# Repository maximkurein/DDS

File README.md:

<p align="center">

</p>

<p align="center">
  <a href="#скачать"><strong>Скачать DDS Studio</strong></a>
  &nbsp;·&nbsp; <a href="#плата">Плата</a>
  &nbsp;·&nbsp; <a href="#прошивка">Прошивка</a>
  &nbsp;·&nbsp; <a href="#dds-studio">DDS Studio</a>
  &nbsp;·&nbsp; <a href="USER_GUIDE.md">Руководство</a>
  &nbsp;·&nbsp; <a href="README_RU.md">Инженерные подробности</a>
</p>

Синтезатор частоты **48–52 МГц** с шагом **1 кГц** и выходом **−10 дБм на 50 Ом**. Сигнал формирует прямой цифровой синтезатор **1508ПЛ8Т** (АО НПЦ «ЭЛВИС») от такта 480 МГц, управляет им контроллер **1887ВЕ7Т**. Частоту задают DIP-переключатели или компьютер через USB-UART и приложение **DDS Studio**.

В репозитории всё изделие: проект платы в KiCad с конструкторской документацией по ГОСТ ЕСКД, прошивка контроллера и настольное приложение для управления и изучения DDS.

<p align="center">
  
  <br><sub>Ревизия F, 120×50 мм, 4 слоя. Рендер KiCad 10 из <code>DDS_48_52.kicad_pcb</code>.</sub>
</p>

## Из чего состоит

| | Часть | Что внутри | Где |
|---|---|---|---|
| 🧩 | **Плата** | схема на 3 листах, плата 4 слоя, Gerber/BOM/CPL для JLCPCB, Э3 и ПЭ3 | [`DDS_48_52.kicad_pro`](DDS_48_52.kicad_pro), [`output/`](output) |
| ⚙️ | **Прошивка D2** | запуск 1508ПЛ8Т по SPI, частота с DIP, бесшовная смена, команды по UART | [`firmware/`](firmware) |
| 🖥️ | **DDS Studio** | регистры, расчёт частоты и спектра, виртуальная плата, опыты, уроки | [`studio/`](studio) |

## Скачать

**DDS Studio 0.3.1 для macOS и Windows** — на странице [релизов](https://github.com/maximkurein/DDS/releases/latest):

| Файл | Что это |
|---|---|
| `DDS-Studio-v0.3.1-macos-universal.dmg` | macOS (Apple Silicon и Intel): перетащите DDS Studio в «Программы» |
| `DDS-Studio-v0.3.1-macos-universal.app.zip` | то же приложение без образа диска |
| `DDS-Studio-v0.3.1-windows-x64-setup.exe` | Windows 10/11: установщик, ярлык в меню «Пуск» и на рабочем столе |
| `DDS-Studio-v0.3.1-windows-x64.zip` | тот же `DDS Studio.exe` без мастера установки |
| `checksum.txt` | контрольные суммы SHA-256 |

Приложение не подписано. Windows SmartScreen: «Подробнее» → «Выполнить в любом случае». macOS при первом запуске: правый клик по приложению → «Открыть», или

```bash
xattr -dr com.apple.quarantine "/Applications/DDS Studio.app"
```

Без платы приложение работает с **виртуальной платой**: все экраны и опыты доступны сразу. Windows и веб-режим собираются из исходников — см. [studio/BUILD.md](studio/BUILD.md).

## Плата

| Узел | Что |
|---|---|
| DDS | 1508ПЛ8Т (D1): 48-битный аккумулятор фазы, 10-битный ЦАП, такт 480 МГц |
| Контроллер | 1887ВЕ7Т (D2), +5 В, тактирование от внутреннего RC 8 МГц |
| Выход | ФНЧ 7-го порядка (срез ≈ 70 МГц) и аттенюатор → XW2, −10 дБм на 50 Ом |
| Такт | S1: внешний вход XW1 или генератор G1 (не устанавливается) |
| Частота | DIP S2 (8 разрядов) + S3 (4 разряда), кнопка «Применить» S4 |
| Связь с ПК | USB-UART на площадках X1, 38400 8N1, логика 5 В |
| Питание | +15 В → DC/DC 1393ЕУ014 (+5 В) → LDO 1158ЕН3.3ВХ (+3,3 В), 1325ЕН1.8У (+1,8 В) |
| Конструкция | 120×50 мм, 4 слоя, JLC04161H-7628, ENIG |

<table>
  <tr>
    <td width="50%"><br><sub><b>Сверху.</b> D1 — справа, D2 — в центре, DIP S2/S3 и кнопка S4 внизу, SMA XW1 (такт) и XW2 (выход).</sub></td>
    <td width="50%"><br><sub><b>Снизу.</b> Элементов нет: полигон земли, сшивка переходными отверстиями по краям, выводы DIP и SMA.</sub></td>
  </tr>
</table>

**Статус.** ERC 0, DRC со сверкой со схемой 0, соединения совпадают с эталоном ревизии F. Это **ещё не выпуск в производство**: посадочные места новых отечественных элементов — заполнители до получения чертежей корпусов, генератор G1 не подтверждён паспортом, нагрев 1325ЕН1.8У и устойчивость 1393ЕУ014 нужно проверить. Подробно — [README_RU.md](README_RU.md), [docs/REVISION_F.md](docs/REVISION_F.md), [docs/design_notes.md](docs/design_notes.md).

Схема и плата открываются в KiCad 10: `DDS_48_52.kicad_pro`. PDF схемы и сборочного чертежа — в [`output/pdf/`](output/pdf), файлы для заказа — в [`output/jlcpcb/`](output/jlcpcb).

## Прошивка

Прошивка контроллера D2 написана на C (avr-gcc, CMake), собирается и прошивается из VS Code/Cursor через JTAG (X3).

- После включения ждёт питание DDS, сбрасывает и настраивает 1508ПЛ8Т, ставит частоту с DIP-переключателей.
- Новая частота включается кнопкой S4 **без разрыва фазы**: запись в неактивный профиль и переключение `SEL_REG`.
- С версии **1.1.0** принимает команды по UART (`?`, `REMOTE`, `W`, `R`, `S`, `RST`, `HOP`, `ST`): в режиме `REMOTE` частотой управляет компьютер.
- Логика проверяется на ПК host-тестами с подменой SPI и таймеров (`cmake --preset host-tests`).

Подробно — [firmware/README.md](firmware/README.md), первая прошивка платы — [USER_GUIDE.md](USER_GUIDE.md).

## DDS Studio

Настольное приложение для управления платой и изучения DDS: ядро на Rust, нативный интерфейс на egui (без WebView) для macOS и Windows, плюс веб-режим на React. Интерфейс на русском.

<p align="center">
  
  <br><sub>Живая блок-схема 1508ПЛ8Т: нажмите на блок — справа его параметры и поля регистров. Снимки — DDS Studio 0.3.0 (egui).</sub>
</p>

<table>
  <tr>
    <td width="50%"><br><sub><b>Частота.</b> Приращение фазы dPh, ошибка сетки, DIP-код, ожидаемый уровень на XW2 и подбор амплитуды.</sub></td>
    <td width="50%"><br><sub><b>Спектр.</b> Бит-в-бит модель канала и БПФ: несущая, гармоники, образы Fclk ± f, спуры усечения фазы.</sub></td>
  </tr>
  <tr>
    <td><br><sub><b>Тракт и шум.</b> АЧХ ФНЧ и аттенюатора с потерями катушек, sin(x)/x, фазовый шум и джиттер.</sub></td>
    <td><br><sub><b>Регистры.</b> 186 регистров по ТО, поля по битам, запись и чтение, экспорт в C-массив для прошивки.</sub></td>
  </tr>
  <tr>
    <td><br><sub><b>ЛЧМ.</b> Встроенный генератор линейной частотной модуляции: пила, треугольник, импульсный режим.</sub></td>
    <td><br><sub><b>Манипуляции.</b> ЧМн, ФМн-2/4/8, АМн, КАМ-16 на профилях с созвездием и последовательностью символов.</sub></td>
  </tr>
  <tr>
    <td><br><sub><b>Перебор.</b> 16 профилей канала 1; прошивка переключает их по таймеру (<code>HOP</code>).</sub></td>
    <td><br><sub><b>Свип.</b> Ступенчатая перестройка 48 → 52 МГц с бесшовной сменой частоты на каждой точке.</sub></td>
  </tr>
  <tr>
    <td><br><sub><b>Плата.</b> Вид по файлу KiCad, назначение каждого элемента, чек-лист первого включения.</sub></td>
    <td><br><sub><b>Подключение.</b> USB-UART, состояние платы (REMOTE, PGOOD, DIP), схема проводов и предупреждения.</sub></td>
  </tr>
  <tr>
    <td><br><sub><b>Академия.</b> 11 уроков от принципа DDS до протокола платы, из каждого — переход к опыту.</sub></td>
    <td><br><sub><b>Ревизии платы.</b> Как исправить плату в KiCad: мастер изменения T1–T8, матрица влияния, ворота ERC/DRC с командами.</sub></td>
  </tr>
  <tr>
    <td colspan="2"><br><sub><b>Светлая тема.</b> Переключается одной кнопкой в верхней панели.</sub></td>
  </tr>
</table>

Подробно о приложении — [studio/README.md](studio/README.md): подключение к плате, протокол, архитектура, сборка.

### Подключение к плате

| USB-UART адаптер | Плата | Сигнал D2 |
|---|---|---|
| RX | X1.1 | TXD0 (PE1) |
| TX | X1.4 | RXD0 (PE0) |
| GND | X1.6 | GND |

> [!WARNING]
> D2 работает от **+5 В** — нужен адаптер с логикой 5 В. Питание адаптера к плате **не подключать**. X1 — это и площадки ISP: на время ISP-программирования адаптер отсоединить. Такт на XW1 — от −10 до +5 дБм.

## Структура репозитория

```
DDS_48_52.kicad_pro, *.kicad_sch, *.kicad_pcb   проект KiCad (ревизия F)
lib/                                            символы, посадочные места, рамка ГОСТ
output/                                         PDF, BOM, нетлист, Gerber/CPL JLCPCB, Э3 (Visio), ПЭ3 (Word)
firmware/                                       прошивка D2 (1887ВЕ7Т), host-тесты
studio/                                         DDS Studio: Rust (egui) + веб-режим React
docs/                                           инженерные примечания, ревизии, уроки
tools/                                          генераторы схемы и платы, выпуск документов
.claude/skills/                                 скиллы Claude Code: разработка и ревизии плат
```

## Документация

| Документ | О чём |
|---|---|
| [START_HERE.md](START_HERE.md) | первый шаг на новой машине: клонирование, окружение, правила работы |
| [USER_GUIDE.md](USER_GUIDE.md) | руководство пользователя: подключение, частота, первая прошивка |
| [README_RU.md](README_RU.md) | плата подробно: листы схемы, пересборка, скрипты, история ревизий |
| [firmware/README.md](firmware/README.md) | прошивка: сборка, отладка, протокол UART (раздел 8.5) |
| [studio/README.md](studio/README.md) | DDS Studio: возможности, подключение, сборка |
| [studio/docs/PROTOCOL_ru.md](studio/docs/PROTOCOL_ru.md) | команды прошивки по UART |
| [docs/REVISION_F.md](docs/REVISION_F.md) | изменения ревизии F и состав КД |

Первоисточник по кристаллу — [ТО 1508ПЛ8Т](https://elvees.ru/typo11/mc/data_sheets/Manual_1508PL8T.pdf) (АО НПЦ «ЭЛВИС», ред. 14.10.2020). PDF производителей в репозиторий не кладём.

## Скиллы Claude Code

Технология «ТЗ → ЭРИ → схема → плата → документы → производство» и выпуск ревизий записаны как скиллы Claude Code в `.claude/skills/` и подхватываются при запуске Claude Code из корня репозитория:

- `pcb-design-pipeline` — сквозная разработка платы (KiCad, ГОСТ ЕСКД, JLCPCB);
- `pcb-revision-eco` — исправления и новая ревизия готовой платы.

Уроки проекта — в [docs/lessons.md](docs/lessons.md).

## Что ещё не проверено

- Плата ревизии F не изготовлена: работа на железе, уровень −10 дБм и тепловой режим не подтверждены.
- Прошивка 1.1.0 проверена host-тестами на ПК; сборка avr-gcc и UART на плате ещё не проверялись.
- Модель DDS Studio — инженерное приближение по ТО и схеме; уровень на XW2 уточняется измерением.

<details>
<summary><b>English summary</b></summary>

Frequency synthesizer 48–52 MHz, 1 kHz step, −10 dBm into 50 Ω, built around the 1508PL8T DDS (Elvees) clocked at 480 MHz and the 1887VE7T controller; board revision F, 120×50 mm, 4 layers, KiCad 10 with GOST ESKD documents and JLCPCB outputs. The repository also holds the controller firmware (C, CMake; UART command protocol since 1.1.0) and **DDS Studio**, a native Rust/egui desktop app (macOS, Windows) with a React web mode with a register map, frequency planner, bit-exact spectrum model, output-filter and phase-noise models, chirp and keying experiments, a virtual board and Russian lessons. Not a production release: new domestic parts still use placeholder land patterns and the board has not been built yet. The repository is mirrored on GitHub and a private Forgejo.

</details>

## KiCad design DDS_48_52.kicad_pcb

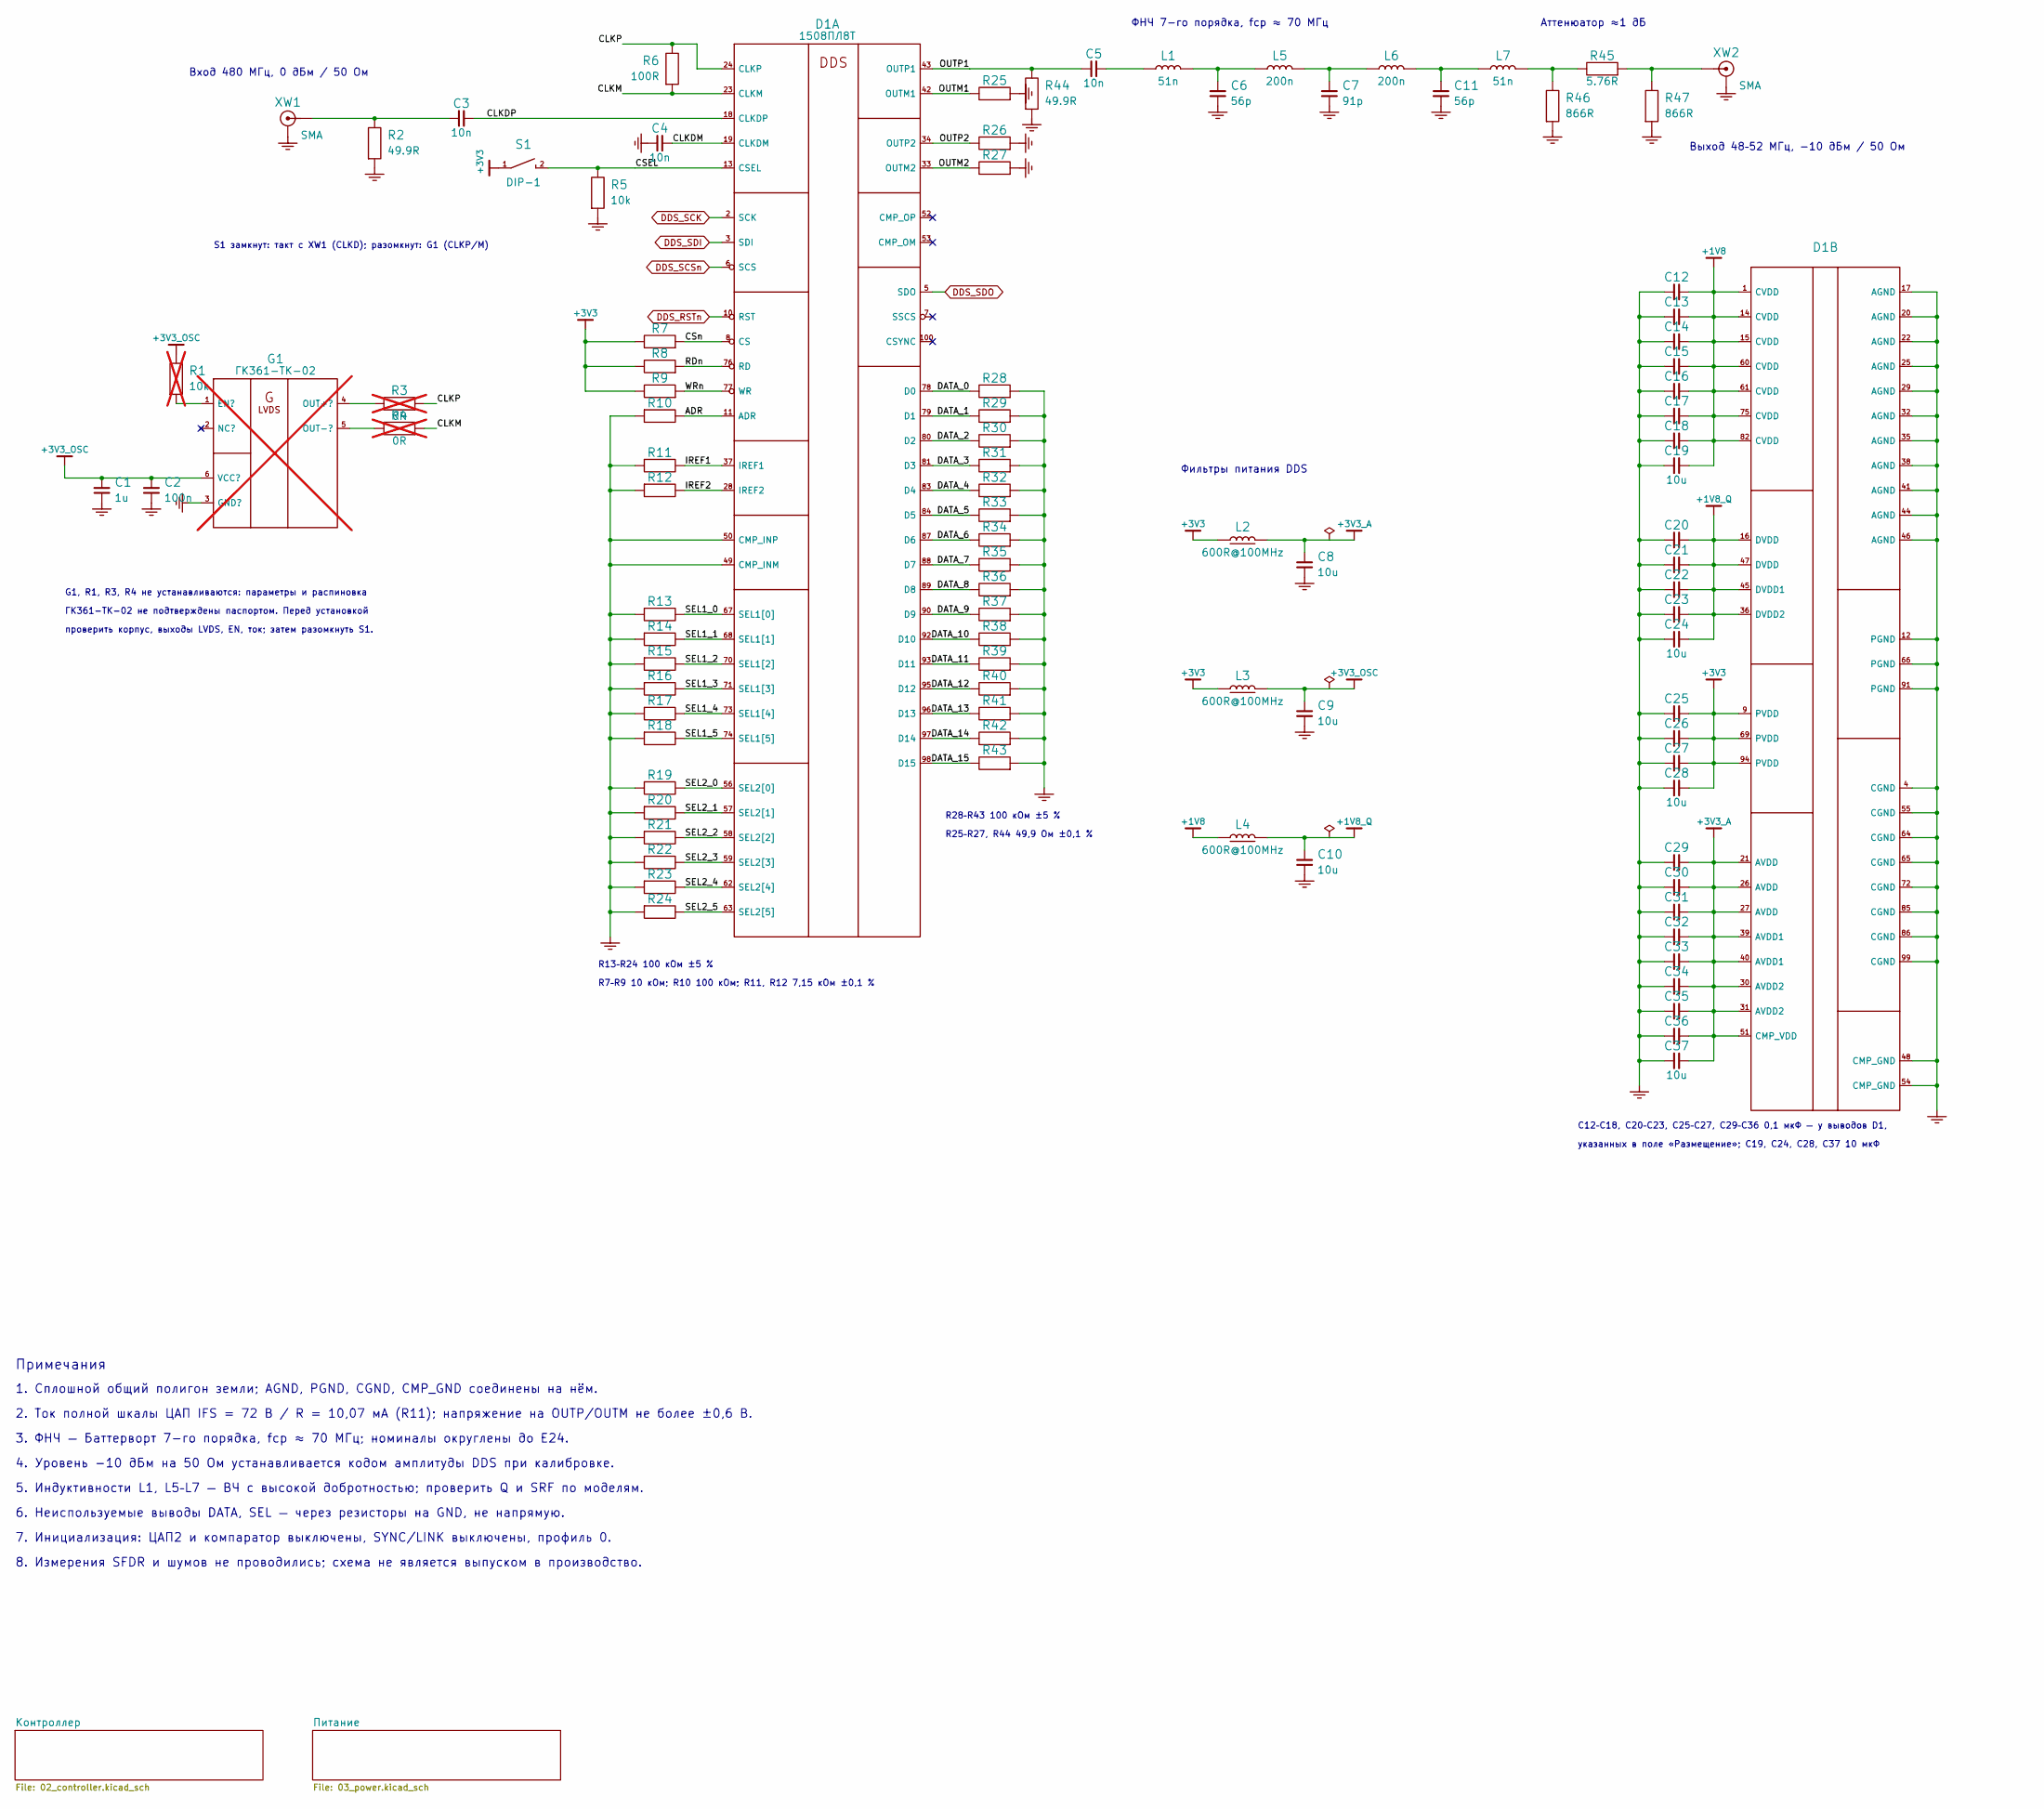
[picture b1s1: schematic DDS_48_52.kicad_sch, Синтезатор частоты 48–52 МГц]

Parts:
C1: 1u; C_0603_1608Metric
C2, C12, C13, C14, C15, C16, C17, C18, C20, C21, C22, C23, C25, C26, C27, C29, C30, C31, C32, C33, C34, C35, C36: 100n; C_0603_1608Metric
C3, C4, C5: 10n; C_0603_1608Metric
C6, C11: 56p; C_0603_1608Metric
C7: 91p; C_0603_1608Metric
C8, C9, C10, C19, C24, C28, C37: 10u; C_0805_2012Metric
D1: 1508ПЛ8Т; LQFP-100_14x14mm_P0.5mm_1508PL8T
G1: ГК361-ТК-02; OSC_6pad_5.0x3.2mm_P1.27mm_GK361_UNVERIFIED; not fitted
L1, L7: 51n; L_0603_1608Metric
L2, L3, L4: 600R@100MHz; L_0603_1608Metric
L5, L6: 200n; L_0603_1608Metric
R1: 10k; R_0603_1608Metric; not fitted
R2, R25, R26, R27, R44: 49.9R; R_0603_1608Metric
R3, R4: 0R; R_0603_1608Metric; not fitted
R5, R7, R8, R9: 10k; R_0603_1608Metric
R6: 100R; R_0603_1608Metric
R10, R13, R14, R15, R16, R17, R18, R19, R20, R21, R22, R23, R24, R28, R29, R30, R31, R32, R33, R34, R35, R36, R37, R38, R39, R40, R41, R42, R43: 100k; R_0603_1608Metric
R11, R12: 7.15k; R_0603_1608Metric
R45: 5.76R; R_0603_1608Metric
R46, R47: 866R; R_0603_1608Metric
S1: DIP-1; SW_DIP_SPSTx01_Slide_9.78x4.72mm_W7.62mm_P2.54mm
XW1, XW2: SMA; SMA_Samtec_SMA-J-P-H-ST-EM1_EdgeMount

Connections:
+1V8: C12.1, C13.1, C14.1, C15.1, C16.1, C17.1, C18.1, C19.1, D1.1 (CVDD), D1.14 (CVDD), D1.15 (CVDD), D1.60 (CVDD), D1.61 (CVDD), D1.75 (CVDD), D1.82 (CVDD), L4.1; also elsewhere on the board
+1V8_Q: C10.1, C20.1, C21.1, C22.1, C23.1, C24.1, D1.16 (DVDD), D1.36 (DVDD2), D1.45 (DVDD1), D1.47 (DVDD), L4.2
+3V3: C25.1, C26.1, C27.1, C28.1, D1.9 (PVDD), D1.69 (PVDD), D1.94 (PVDD), L2.1, L3.1, R7.1, R8.1, R9.1, S1.1; also elsewhere on the board
+3V3_A: C8.1, C29.1, C30.1, C31.1, C32.1, C33.1, C34.1, C35.1, C36.1, C37.1, D1.21 (AVDD), D1.26 (AVDD), D1.27 (AVDD), D1.30 (AVDD2), D1.31 (AVDD2), D1.39 (AVDD1), D1.40 (AVDD1), D1.51 (CMP_VDD), L2.2
+3V3_OSC: C1.1, C2.1, C9.1, G1.6 (VCC?), L3.2, R1.1
/ADR: D1.11 (ADR), R10.1
/CLKDM: C4.1, D1.19 (CLKDM)
/CLKDP: C3.2, D1.18 (CLKDP)
/CLKM: D1.23 (CLKM), R4.2, R6.2
/CLKP: D1.24 (CLKP), R3.2, R6.1
/CSEL: D1.13 (CSEL), R5.1, S1.2
/CSn: D1.8 (CS), R7.2
/DATA_0: D1.78 (D0), R28.1
/DATA_1: D1.79 (D1), R29.1
/DATA_2: D1.80 (D2), R30.1
/DATA_3: D1.81 (D3), R31.1
/DATA_4: D1.83 (D4), R32.1
/DATA_5: D1.84 (D5), R33.1
/DATA_6: D1.87 (D6), R34.1
/DATA_7: D1.88 (D7), R35.1
/DATA_8: D1.89 (D8), R36.1
/DATA_9: D1.90 (D9), R37.1
/DATA_10: D1.92 (D10), R38.1
/DATA_11: D1.93 (D11), R39.1
/DATA_12: D1.95 (D12), R40.1
/DATA_13: D1.96 (D13), R41.1
/DATA_14: D1.97 (D14), R42.1
/DATA_15: D1.98 (D15), R43.1
/IREF1: D1.37 (IREF1), R11.1
/IREF2: D1.28 (IREF2), R12.1
/OUTM1: D1.42 (OUTM1), R25.1
/OUTM2: D1.33 (OUTM2), R27.1
/OUTP1: C5.1, D1.43 (OUTP1), R44.1
/OUTP2: D1.34 (OUTP2), R26.1
/RDn: D1.76 (RD), R8.2
/SEL1_0: D1.67 (SEL1[0]), R13.1
/SEL1_1: D1.68 (SEL1[1]), R14.1
/SEL1_2: D1.70 (SEL1[2]), R15.1
/SEL1_3: D1.71 (SEL1[3]), R16.1
/SEL1_4: D1.73 (SEL1[4]), R17.1
/SEL1_5: D1.74 (SEL1[5]), R18.1
/SEL2_0: D1.56 (SEL2[0]), R19.1
/SEL2_1: D1.57 (SEL2[1]), R20.1
/SEL2_2: D1.58 (SEL2[2]), R21.1
/SEL2_3: D1.59 (SEL2[3]), R22.1
/SEL2_4: D1.62 (SEL2[4]), R23.1
/SEL2_5: D1.63 (SEL2[5]), R24.1
/WRn: D1.77 (WR), R9.2
DDS_RSTn: D1.10 (RST); also elsewhere on the board
DDS_SCK: D1.2 (SCK); also elsewhere on the board
DDS_SCSn: D1.6 (SCS); also elsewhere on the board
DDS_SDI: D1.3 (SDI); also elsewhere on the board
DDS_SDO: D1.5 (SDO); also elsewhere on the board
GND: C1.2, C2.2, C4.2, C6.2, C7.2, C8.2, C9.2, C10.2, C11.2, C12.2, C13.2, C14.2, C15.2, C16.2, C17.2, C18.2, C19.2, C20.2, C21.2, C22.2, C23.2, C24.2, C25.2, C26.2, C27.2, C28.2, C29.2, C30.2, C31.2, C32.2, C33.2, C34.2, C35.2, C36.2, C37.2, D1.4 (CGND), D1.12 (PGND), D1.17 (AGND), D1.20 (AGND), D1.22 (AGND), D1.25 (AGND), D1.29 (AGND), D1.32 (AGND), D1.35 (AGND), D1.38 (AGND), D1.41 (AGND), D1.44 (AGND), D1.46 (AGND), D1.48 (CMP_GND), D1.49 (CMP_INM), D1.50 (CMP_INP), D1.54 (CMP_GND), D1.55 (CGND), D1.64 (CGND), D1.65 (CGND), D1.66 (PGND), D1.72 (CGND), D1.85 (CGND), D1.86 (CGND), D1.91 (PGND), D1.99 (CGND), G1.3 (GND?), R2.2, R5.2, R10.2, R11.2, R12.2, R13.2, R14.2, R15.2, R16.2, R17.2, R18.2, R19.2, R20.2, R21.2, R22.2, R23.2, R24.2, R25.2, R26.2, R27.2, R28.2, R29.2, R30.2, R31.2, R32.2, R33.2, R34.2, R35.2, R36.2, R37.2, R38.2, R39.2, R40.2, R41.2, R42.2, R43.2, R44.2, R46.2, R47.2, XW1.2, XW2.2; also elsewhere on the board
unnamed: C3.1, R2.1, XW1.1
unnamed: C5.2, L1.1
unnamed: C6.1, L1.2, L5.1
unnamed: C7.1, L5.2, L6.1
unnamed: C11.1, L6.2, L7.1
unnamed: G1.1 (EN?), R1.2
unnamed: G1.4 (OUT+?), R3.1
unnamed: G1.5 (OUT-?), R4.1
unnamed: L7.2, R45.1, R46.1
unnamed: R45.2, R47.1, XW2.1

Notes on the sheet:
6. Неиспользуемые выводы DATA, SEL — через резисторы на GND, не напрямую.
S1 замкнут: такт с XW1 (CLKD); разомкнут: G1 (CLKP/M)
Вход 480 МГц, 0 дБм / 50 Ом
Выход 48–52 МГц, −10 дБм / 50 Ом
ФНЧ 7-го порядка, fср ≈ 70 МГц
8. Измерения SFDR и шумов не проводились; схема не является выпуском в производство.
R28–R43 100 кОм ±5 %
3. ФНЧ — Баттерворт 7-го порядка, fср ≈ 70 МГц; номиналы округлены до E24.
5. Индуктивности L1, L5–L7 — ВЧ с высокой добротностью; проверить Q и SRF по моделям.
R13–R24 100 кОм ±5 %
2. Ток полной шкалы ЦАП IFS = 72 В / R = 10,07 мА (R11); напряжение на OUTP/OUTM не более ±0,6 В.
C12–C18, C20–C23, C25–C27, C29–C36 0,1 мкФ — у выводов D1,
R7–R9 10 кОм; R10 100 кОм; R11, R12 7,15 кОм ±0,1 %
7. Инициализация: ЦАП2 и компаратор выключены, SYNC/LINK выключены, профиль 0.
G1, R1, R3, R4 не устанавливаются: параметры и распиновка
R25–R27, R44 49,9 Ом ±0,1 %
4. Уровень −10 дБм на 50 Ом устанавливается кодом амплитуды DDS при калибровке.
указанных в поле «Размещение»; C19, C24, C28, C37 10 мкФ
проверить корпус, выходы LVDS, EN, ток; затем разомкнуть S1.
1. Сплошной общий полигон земли; AGND, PGND, CGND, CMP_GND соединены на нём.
Примечания
Фильтры питания DDS
ГК361-ТК-02 не подтверждены паспортом. Перед установкой
Аттенюатор ≈1 дБ

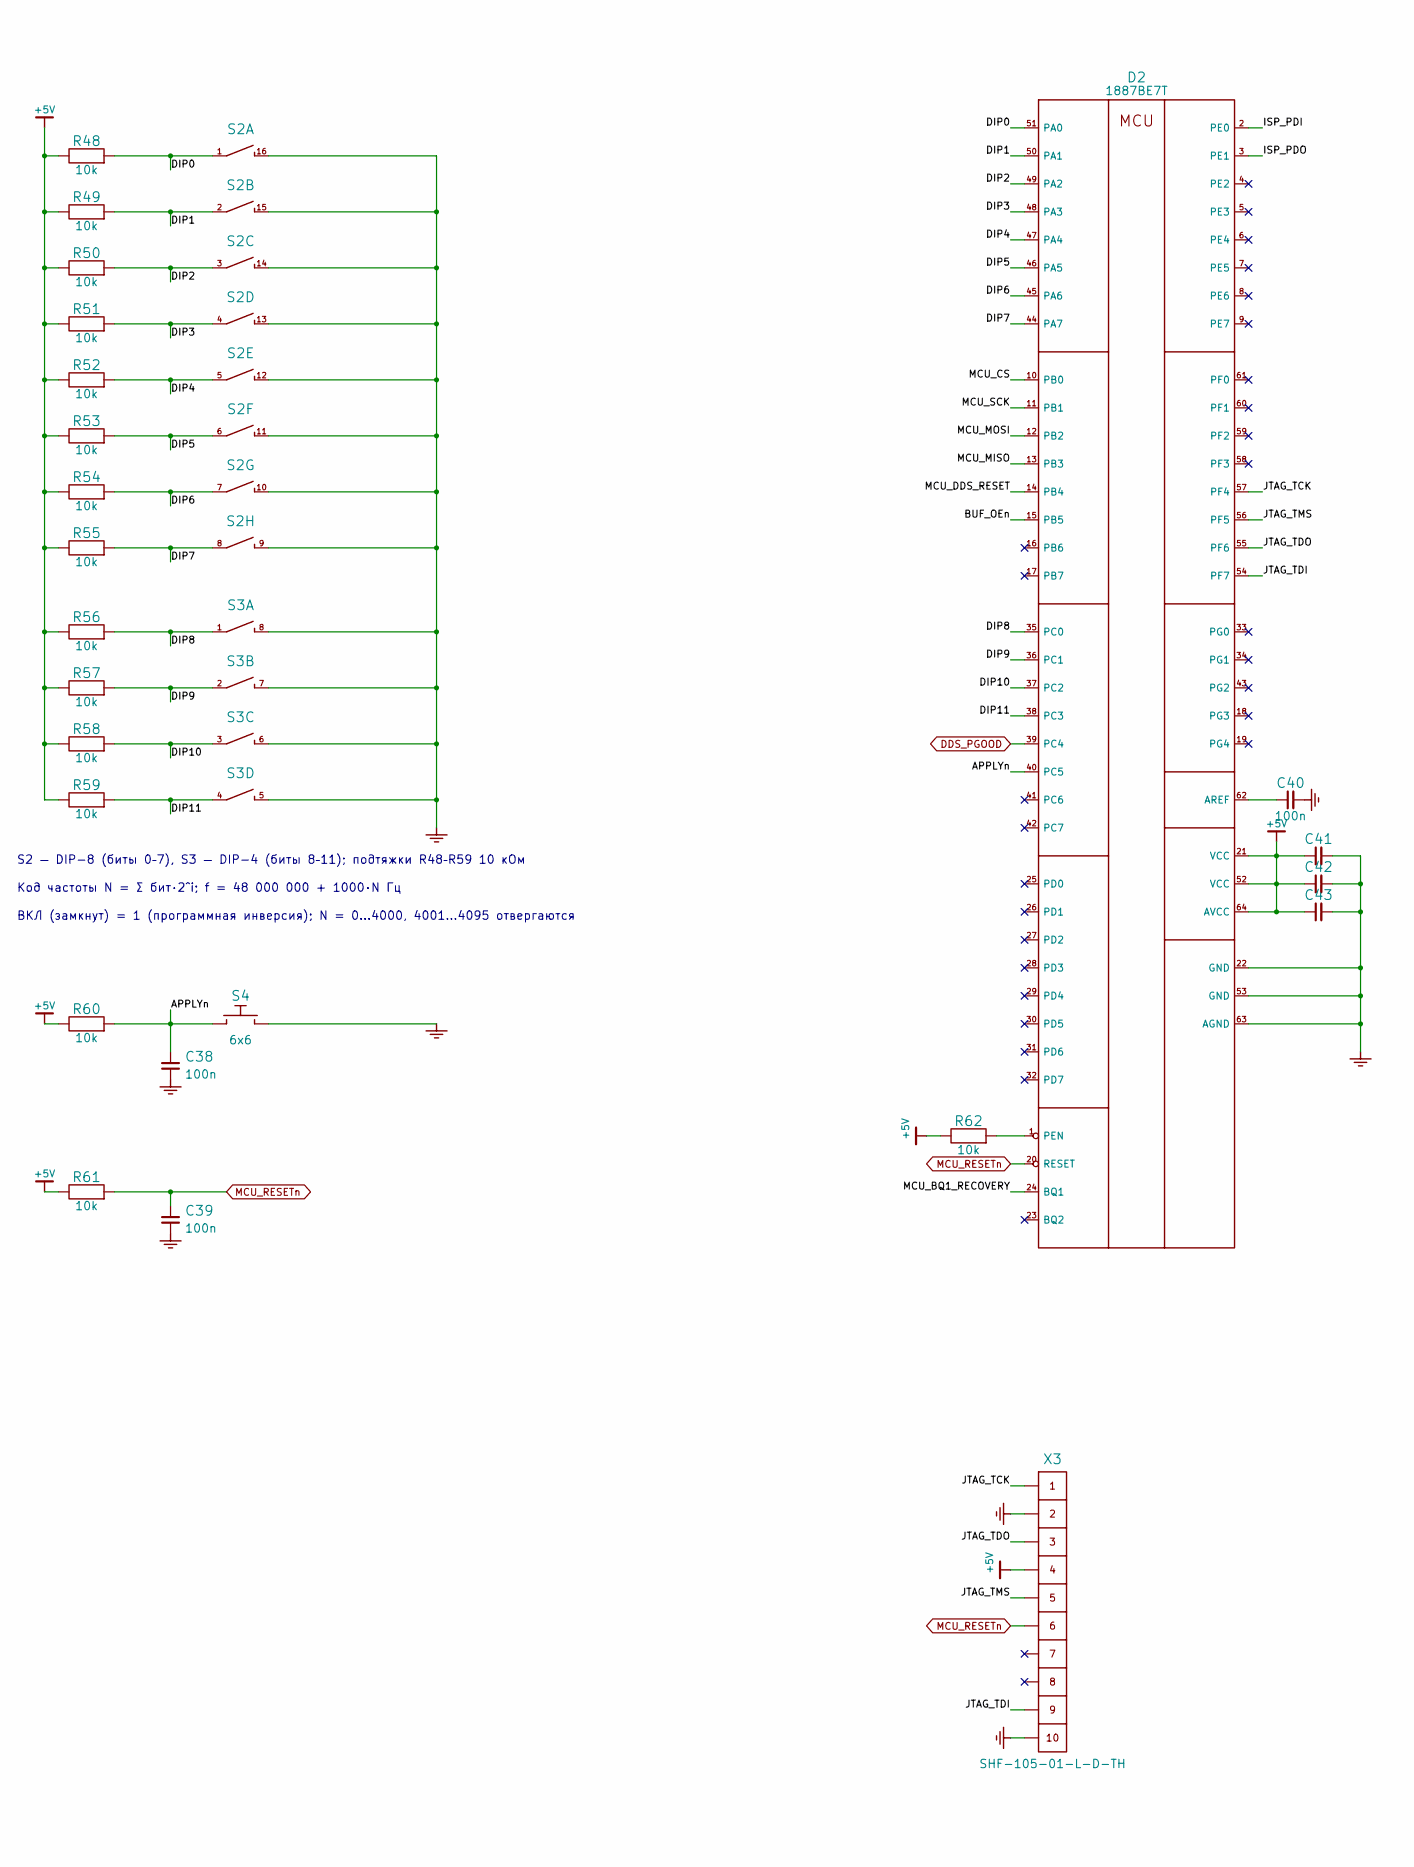
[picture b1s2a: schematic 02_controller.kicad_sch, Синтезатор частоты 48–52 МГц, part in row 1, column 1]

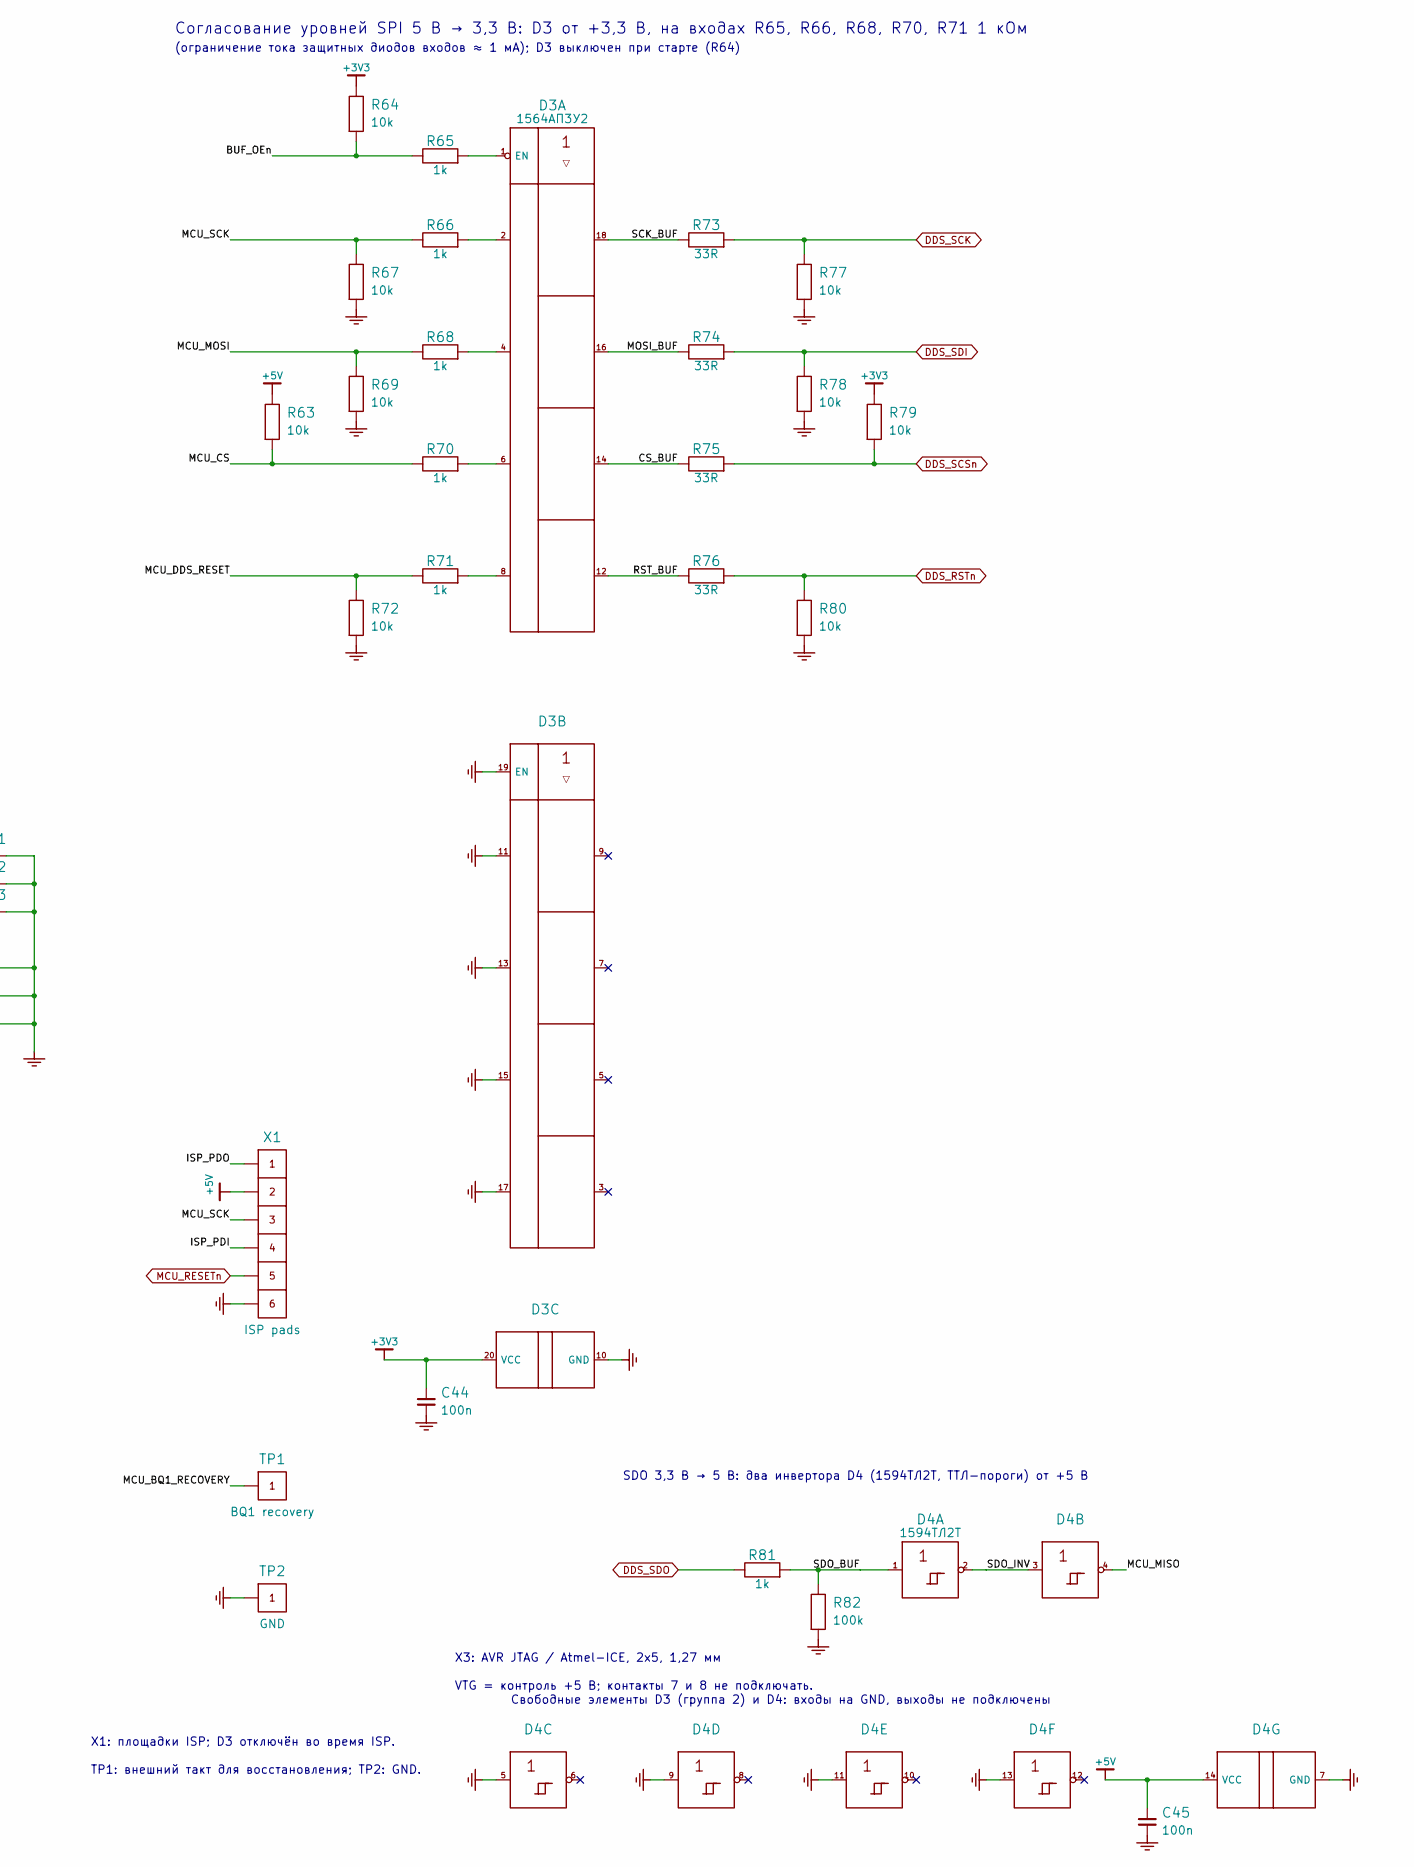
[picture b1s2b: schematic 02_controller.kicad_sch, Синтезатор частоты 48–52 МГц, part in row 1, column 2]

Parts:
C38, C39, C40, C41, C42, C43, C44, C45: 100n; C_0603_1608Metric
D2: 1887ВЕ7Т; CQFP-64_4203.64-2_14x14mm_P0.8mm_1887VE7T
D3: 1564АП3У2; SOIC-20W_1564AP3U2_PLACEHOLDER
D4: 1594ТЛ2Т; SOIC-14_1594TL2T_PLACEHOLDER
R48, R49, R50, R51, R52, R53, R54, R55, R56, R57, R58, R59, R60, R61, R62, R63, R64, R67, R69, R72, R77, R78, R79, R80: 10k; R_0603_1608Metric
R65, R66, R68, R70, R71, R81: 1k; R_0603_1608Metric
R73, R74, R75, R76: 33R; R_0603_1608Metric
R82: 100k; R_0603_1608Metric
S2: DIP-8; SW_DIP_SPSTx08_Slide_9.78x22.5mm_W7.62mm_P2.54mm
S3: DIP-4; SW_DIP_SPSTx04_Slide_9.78x12.34mm_W7.62mm_P2.54mm
S4: 6x6; SW_PUSH_6mm
TP1: BQ1 recovery; TestPad_D1.5mm
TP2: GND; TestPad_D1.5mm
X1: ISP pads; ISP_Pads_2x03_P2.54mm
X3: SHF-105-01-L-D-TH; Samtec_SHF-105-01-L-D-TH

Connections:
+3V3: C44.1, D3.20 (VCC), R64.1, R79.1; also elsewhere on the board
+5V: C41.1, C42.1, C43.1, C45.1, D2.21 (VCC), D2.52 (VCC), D2.64 (AVCC), D4.14 (VCC), R48.1, R49.1, R50.1, R51.1, R52.1, R53.1, R54.1, R55.1, R56.1, R57.1, R58.1, R59.1, R60.1, R61.1, R62.1, R63.1, X1.2, X3.4; also elsewhere on the board
/Контроллер/APPLYn: C38.1, D2.40 (PC5), R60.2, S4.1
/Контроллер/BUF_OEn: D2.15 (PB5), R64.2, R65.1
/Контроллер/CS_BUF: D3.14, R75.1
/Контроллер/DIP0: D2.51 (PA0), R48.2, S2.1
/Контроллер/DIP1: D2.50 (PA1), R49.2, S2.2
/Контроллер/DIP2: D2.49 (PA2), R50.2, S2.3
/Контроллер/DIP3: D2.48 (PA3), R51.2, S2.4
/Контроллер/DIP4: D2.47 (PA4), R52.2, S2.5
/Контроллер/DIP5: D2.46 (PA5), R53.2, S2.6
/Контроллер/DIP6: D2.45 (PA6), R54.2, S2.7
/Контроллер/DIP7: D2.44 (PA7), R55.2, S2.8
/Контроллер/DIP8: D2.35 (PC0), R56.2, S3.1
/Контроллер/DIP9: D2.36 (PC1), R57.2, S3.2
/Контроллер/DIP10: D2.37 (PC2), R58.2, S3.3
/Контроллер/DIP11: D2.38 (PC3), R59.2, S3.4
/Контроллер/ISP_PDI: D2.2 (PE0), X1.4
/Контроллер/ISP_PDO: D2.3 (PE1), X1.1
/Контроллер/JTAG_TCK: D2.57 (PF4), X3.1
/Контроллер/JTAG_TDI: D2.54 (PF7), X3.9
/Контроллер/JTAG_TDO: D2.55 (PF6), X3.3
/Контроллер/JTAG_TMS: D2.56 (PF5), X3.5
/Контроллер/MCU_BQ1_RECOVERY: D2.24 (BQ1), TP1.1
/Контроллер/MCU_CS: D2.10 (PB0), R63.2, R70.1
/Контроллер/MCU_DDS_RESET: D2.14 (PB4), R71.1, R72.1
/Контроллер/MCU_MISO: D2.13 (PB3), D4.4
/Контроллер/MCU_MOSI: D2.12 (PB2), R68.1, R69.1
/Контроллер/MCU_SCK: D2.11 (PB1), R66.1, R67.1, X1.3
/Контроллер/MOSI_BUF: D3.16, R74.1
/Контроллер/RST_BUF: D3.12, R76.1
/Контроллер/SCK_BUF: D3.18, R73.1
/Контроллер/SDO_BUF: D4.1, R81.2, R82.1
/Контроллер/SDO_INV: D4.2, D4.3
DDS_PGOOD: D2.39 (PC4); also elsewhere on the board
DDS_RSTn: R76.2, R80.1; also elsewhere on the board
DDS_SCK: R73.2, R77.1; also elsewhere on the board
DDS_SCSn: R75.2, R79.2; also elsewhere on the board
DDS_SDI: R74.2, R78.1; also elsewhere on the board
DDS_SDO: R81.1; also elsewhere on the board
GND: C38.2, C39.2, C40.2, C41.2, C42.2, C43.2, C44.2, C45.2, D2.22 (GND), D2.53 (GND), D2.63 (AGND), D3.10 (GND), D3.11, D3.13, D3.15, D3.17, D3.19 (EN), D4.5, D4.7 (GND), D4.9, D4.11, D4.13, R67.2, R69.2, R72.2, R77.2, R78.2, R80.2, R82.2, S2.9, S2.10, S2.11, S2.12, S2.13, S2.14, S2.15, S2.16, S3.5, S3.6, S3.7, S3.8, S4.2, TP2.1, X1.6, X3.2, X3.10; also elsewhere on the board
MCU_RESETn: C39.1, D2.20 (RESET), R61.2, X1.5, X3.6; also elsewhere on the board
unnamed: C40.1, D2.62 (AREF)
unnamed: D2.1 (PEN), R62.2
unnamed: D3.2, R66.2
unnamed: D3.4, R68.2
unnamed: D3.6, R70.2
unnamed: D3.8, R71.2
unnamed: D3.1 (EN), R65.2

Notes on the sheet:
Код частоты N = Σ бит·2^i; f = 48 000 000 + 1000·N Гц
ВКЛ (замкнут) = 1 (программная инверсия); N = 0…4000, 4001…4095 отвергаются
Свободные элементы D3 (группа 2) и D4: входы на GND, выходы не подключены
S2 — DIP-8 (биты 0–7), S3 — DIP-4 (биты 8–11); подтяжки R48–R59 10 кОм
(ограничение тока защитных диодов входов ≈ 1 мА); D3 выключен при старте (R64)
SDO 3,3 В → 5 В: два инвертора D4 (1594ТЛ2Т, ТТЛ-пороги) от +5 В
Согласование уровней SPI 5 В → 3,3 В: D3 от +3,3 В, на входах R65, R66, R68, R70, R71 1 кОм
TP1: внешний такт для восстановления; TP2: GND.
VTG = контроль +5 В; контакты 7 и 8 не подключать.
X1: площадки ISP; D3 отключён во время ISP.
X3: AVR JTAG / Atmel-ICE, 2x5, 1,27 мм

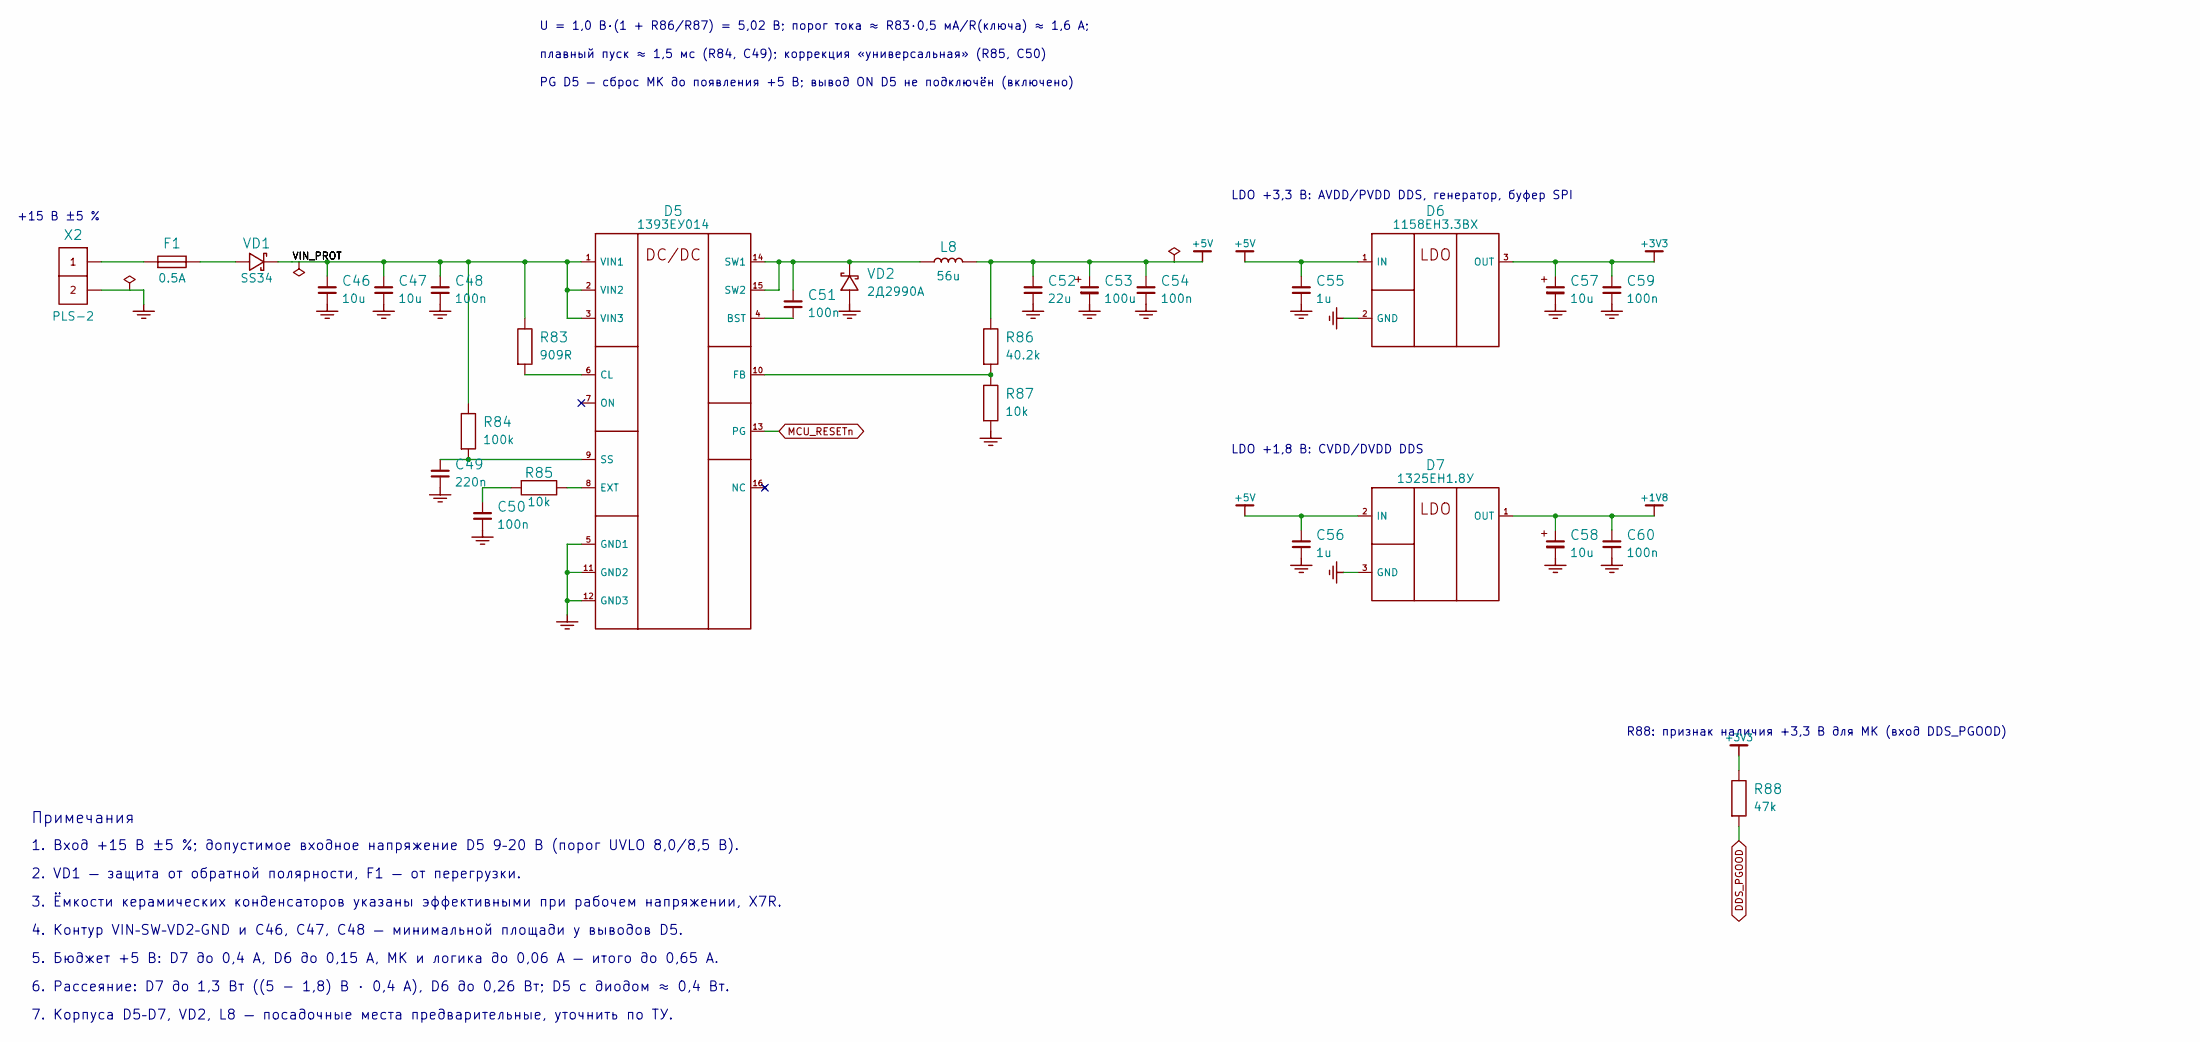
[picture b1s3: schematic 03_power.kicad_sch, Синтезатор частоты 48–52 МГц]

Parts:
C46, C47: 10u; C_1206_3216Metric
C48, C50, C51, C54, C59, C60: 100n; C_0603_1608Metric
C49: 220n; C_0603_1608Metric
C52: 22u; C_1206_3216Metric
C53: 100u; CP_EIA-7343-31_Kemet-D
C55, C56: 1u; C_0603_1608Metric
C57, C58: 10u; CP_EIA-3528-21_Kemet-B
D5: 1393ЕУ014; 4112.16-15.01_1393EU014_PLACEHOLDER
D6: 1158ЕН3.3ВХ; KT-93-1_PLACEHOLDER
D7: 1325ЕН1.8У; KT-93-1_PLACEHOLDER
F1: 0.5A; Fuse_1206_3216Metric
L8: 56u; L_10.4x10.4_L8_UNSELECTED_PLACEHOLDER
R83: 909R; R_0603_1608Metric
R84: 100k; R_0603_1608Metric
R85, R87: 10k; R_0603_1608Metric
R86: 40.2k; R_0603_1608Metric
R88: 47k; R_0603_1608Metric
VD1: SS34; D_SMA
VD2: 2Д2990А; D_SMA_2D2990A_PLACEHOLDER
X2: PLS-2; PinHeader_1x02_P2.54mm_Vertical

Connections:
+1V8: C58.1, C60.1, D7.1 (OUT); also elsewhere on the board
+3V3: C57.1, C59.1, D6.3 (OUT), R88.1; also elsewhere on the board
+5V: C52.1, C53.1, C54.1, C55.1, C56.1, D6.1 (IN), D7.2 (IN), L8.2, R86.1; also elsewhere on the board
/Питание/VIN_PROT: C46.1, C47.1, C48.1, D5.1 (VIN1), D5.2 (VIN2), D5.3 (VIN3), R83.1, R84.1, VD1.1 (K)
DDS_PGOOD: R88.2; also elsewhere on the board
GND: C46.2, C47.2, C48.2, C49.2, C50.2, C52.2, C53.2, C54.2, C55.2, C56.2, C57.2, C58.2, C59.2, C60.2, D5.5 (GND1), D5.11 (GND2), D5.12 (GND3), D6.2 (GND), D7.3 (GND), R87.2, VD2.2 (A), X2.2; also elsewhere on the board
MCU_RESETn: D5.13 (PG); also elsewhere on the board
unnamed: C50.1, R85.2
unnamed: C51.1, D5.4 (BST)
unnamed: D5.6 (CL), R83.2
unnamed: D5.8 (EXT), R85.1
unnamed: D5.10 (FB), R86.2, R87.1
unnamed: C49.1, D5.9 (SS), R84.2
unnamed: C51.2, D5.14 (SW1), D5.15 (SW2), L8.1, VD2.1 (K)
unnamed: F1.1, X2.1
unnamed: F1.2, VD1.2 (A)

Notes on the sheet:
6. Рассеяние: D7 до 1,3 Вт ((5 − 1,8) В · 0,4 А), D6 до 0,26 Вт; D5 с диодом ≈ 0,4 Вт.
U = 1,0 В·(1 + R86/R87) = 5,02 В; порог тока ≈ R83·0,5 мА/R(ключа) ≈ 1,6 А;
5. Бюджет +5 В: D7 до 0,4 А, D6 до 0,15 А, МК и логика до 0,06 А — итого до 0,65 А.
1. Вход +15 В ±5 %; допустимое входное напряжение D5 9–20 В (порог UVLO 8,0/8,5 В).
Примечания
+15 В ±5 %
3. Ёмкости керамических конденсаторов указаны эффективными при рабочем напряжении, X7R.
R88: признак наличия +3,3 В для МК (вход DDS_PGOOD)
плавный пуск ≈ 1,5 мс (R84, C49); коррекция «универсальная» (R85, C50)
LDO +3,3 В: AVDD/PVDD DDS, генератор, буфер SPI
4. Контур VIN–SW–VD2–GND и C46, C47, C48 — минимальной площади у выводов D5.
7. Корпуса D5–D7, VD2, L8 — посадочные места предварительные, уточнить по ТУ.
2. VD1 — защита от обратной полярности, F1 — от перегрузки.
LDO +1,8 В: CVDD/DVDD DDS
PG D5 — сброс МК до появления +5 В; вывод ON D5 не подключён (включено)
